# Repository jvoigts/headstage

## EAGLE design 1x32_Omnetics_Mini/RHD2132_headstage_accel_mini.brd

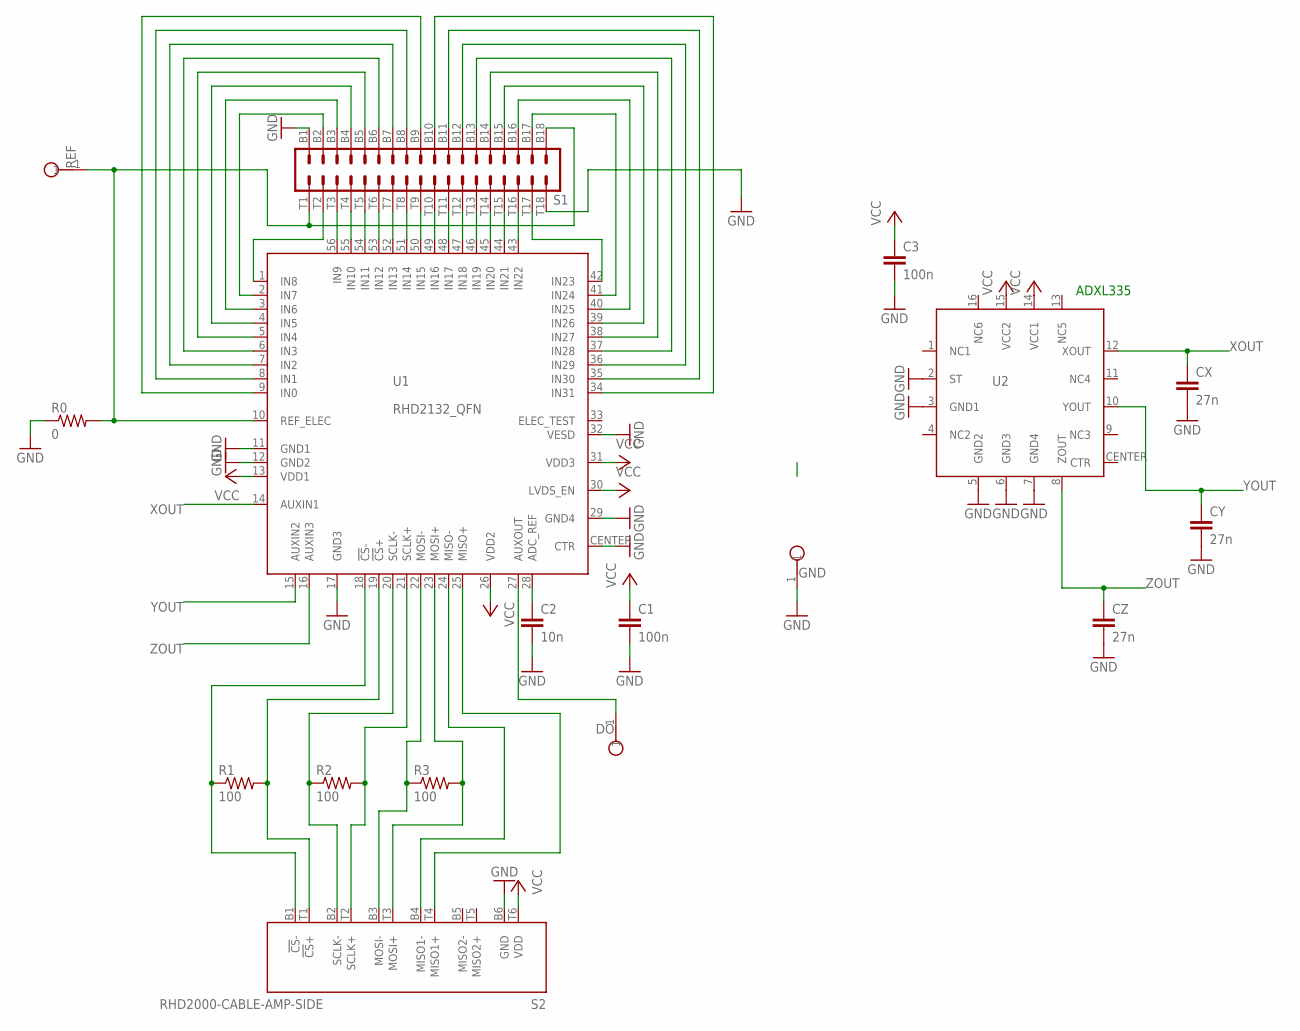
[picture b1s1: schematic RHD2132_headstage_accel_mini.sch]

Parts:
C1, C3: 100n; 0201
C2: 10n; 0201
CX: 27n; 0201
CY: 27n; 0201
CZ: 27n; 0201
DO: TESTPOINT_SMALL
GND: TESTPOINT_SMALL
R0: 0; 0201
R1, R2, R3: 100; 0201
REF: TESTPOINT_SMALL
S1: OMNETICS_A79025
S2: RHD2000-CABLE-AMP-SIDE; OMNETICS_PZN-12-AA
U1: RHD2132_QFN; QFN56_8_X_8_LARGE
U2: ADXL335

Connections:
GND: C1.2, C2.2, C3.2, CX.2, CY.2, CZ.2, GND.1, R0.1, S1.B1, S1.T18, S2.B6 (GND), U1.11 (GND1), U1.12 (GND2), U1.17 (GND3), U1.29 (GND4), U1.32 (VESD), U1.CENTER (CTR), U2.2 (ST), U2.3 (GND1), U2.5 (GND2), U2.6 (GND3), U2.7 (GND4)
unnamed: R0.2, REF.1, S1.B18, S1.T1, U1.10 (REF_ELEC)
unnamed: S1.B3, U1.3 (IN6)
unnamed: S1.B2, U1.2 (IN7)
unnamed: S1.B4, U1.4 (IN5)
unnamed: S1.B5, U1.5 (IN4)
unnamed: S1.B6, U1.6 (IN3)
unnamed: S1.B7, U1.7 (IN2)
unnamed: S1.B8, U1.8 (IN1)
unnamed: S1.B9, U1.9 (IN0)
unnamed: S1.B10, U1.34 (IN31)
unnamed: R1.1, S2.B1 (!CS!-), U1.18 (!CS!-)
unnamed: S1.B17, U1.41 (IN24)
unnamed: S1.B16, U1.40 (IN25)
unnamed: S1.B15, U1.39 (IN26)
unnamed: S1.B14, U1.38 (IN27)
unnamed: S1.B13, U1.37 (IN28)
unnamed: S1.B12, U1.36 (IN29)
unnamed: S1.B11, U1.35 (IN30)
unnamed: S1.T9, U1.50 (IN15)
unnamed: S1.T8, U1.51 (IN14)
unnamed: S1.T7, U1.52 (IN13)
unnamed: S1.T3, U1.56 (IN9)
unnamed: S1.T4, U1.55 (IN10)
unnamed: S1.T5, U1.54 (IN11)
unnamed: S1.T6, U1.53 (IN12)
unnamed: S1.T10, U1.49 (IN16)
unnamed: S1.T11, U1.48 (IN17)
unnamed: S1.T12, U1.47 (IN18)
unnamed: S1.T13, U1.46 (IN19)
unnamed: S1.T14, U1.45 (IN20)
unnamed: S1.T15, U1.44 (IN21)
unnamed: S1.T16, U1.43 (IN22)
unnamed: S1.T2, U1.1 (IN8)
unnamed: S1.T17, U1.42 (IN23)
unnamed: R1.2, S2.T1 (!CS!+), U1.19 (!CS!+)
unnamed: R2.1, S2.B2 (SCLK-), U1.20 (SCLK-)
unnamed: R2.2, S2.T2 (SCLK+), U1.21 (SCLK+)
unnamed: R3.1, S2.B3 (MOSI-), U1.22 (MOSI-)
unnamed: R3.2, S2.T3 (MOSI+), U1.23 (MOSI+)
unnamed: S2.B4 (MISO1-), U1.24 (MISO-)
unnamed: S2.T4 (MISO1+), U1.25 (MISO+)
unnamed: C2.1, U1.28 (ADC_REF)
unnamed: DO.1, U1.27 (AUXOUT)
VCC: C1.1, C3.1, S2.T6 (VDD), U1.13 (VDD1), U1.26 (VDD2), U1.30 (LVDS_EN), U1.31 (VDD3), U2.14 (VCC1), U2.15 (VCC2)
XOUT: CX.1, U1.14 (AUXIN1), U2.12 (XOUT)
YOUT: CY.1, U1.15 (AUXIN2), U2.10 (YOUT)
ZOUT: CZ.1, U1.16 (AUXIN3), U2.8 (ZOUT)

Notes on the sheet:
ADXL335

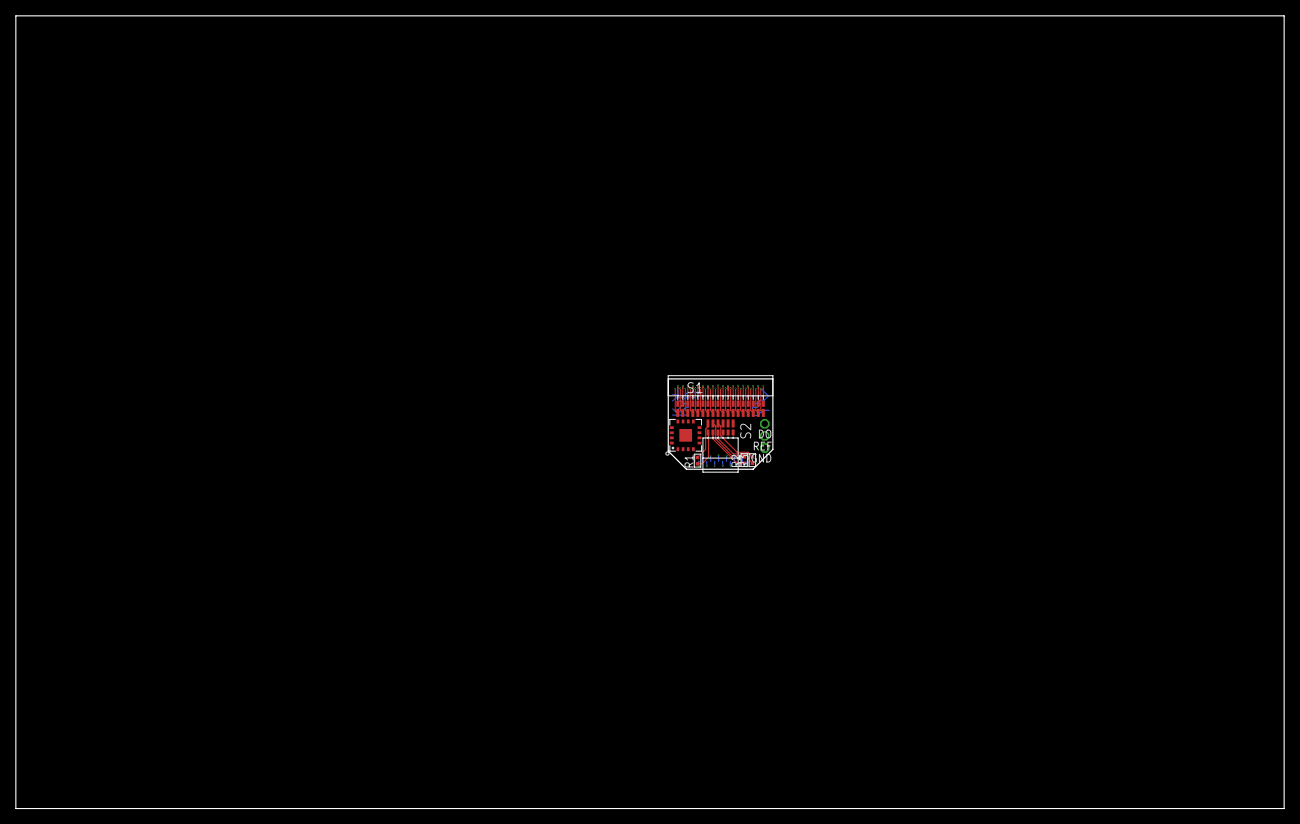
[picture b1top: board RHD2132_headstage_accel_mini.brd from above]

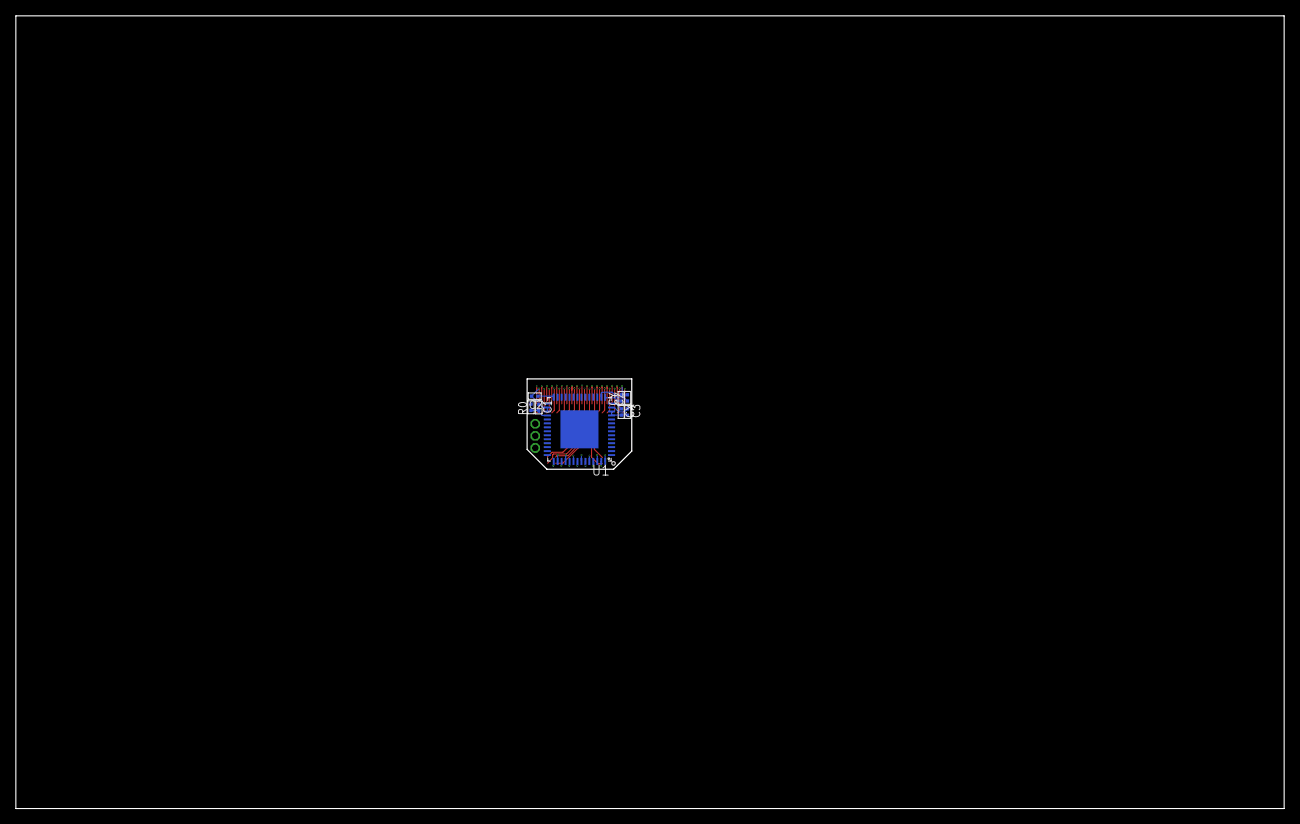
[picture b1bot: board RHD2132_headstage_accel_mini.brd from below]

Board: 4 copper layers, 160.0 x 100.0 mm, 17 parts (8 on the bottom side), 48 nets.

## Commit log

2017-10-19 initial commit basic spacing on smaller 32ch hs
2017-10-23 started some routing
